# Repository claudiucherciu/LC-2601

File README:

# LibreCube LC-2601 GPS Module

## Overview
The LC-2601 GPS Module is a standalone board that integrates an
GPS receiver and makes its output in terms of position, altitude,
and time available via the CAN bus interface.

## Authors
* Claudiu Cherciu <claudiucherciu@gmail.com>
* Dominik Marszk <dmarszk@gmail.com>
* Artur Scholz <artur.scholz@cubesat.de>

## Acknowledgements
Supported by the ESOC Cybernetic Club.

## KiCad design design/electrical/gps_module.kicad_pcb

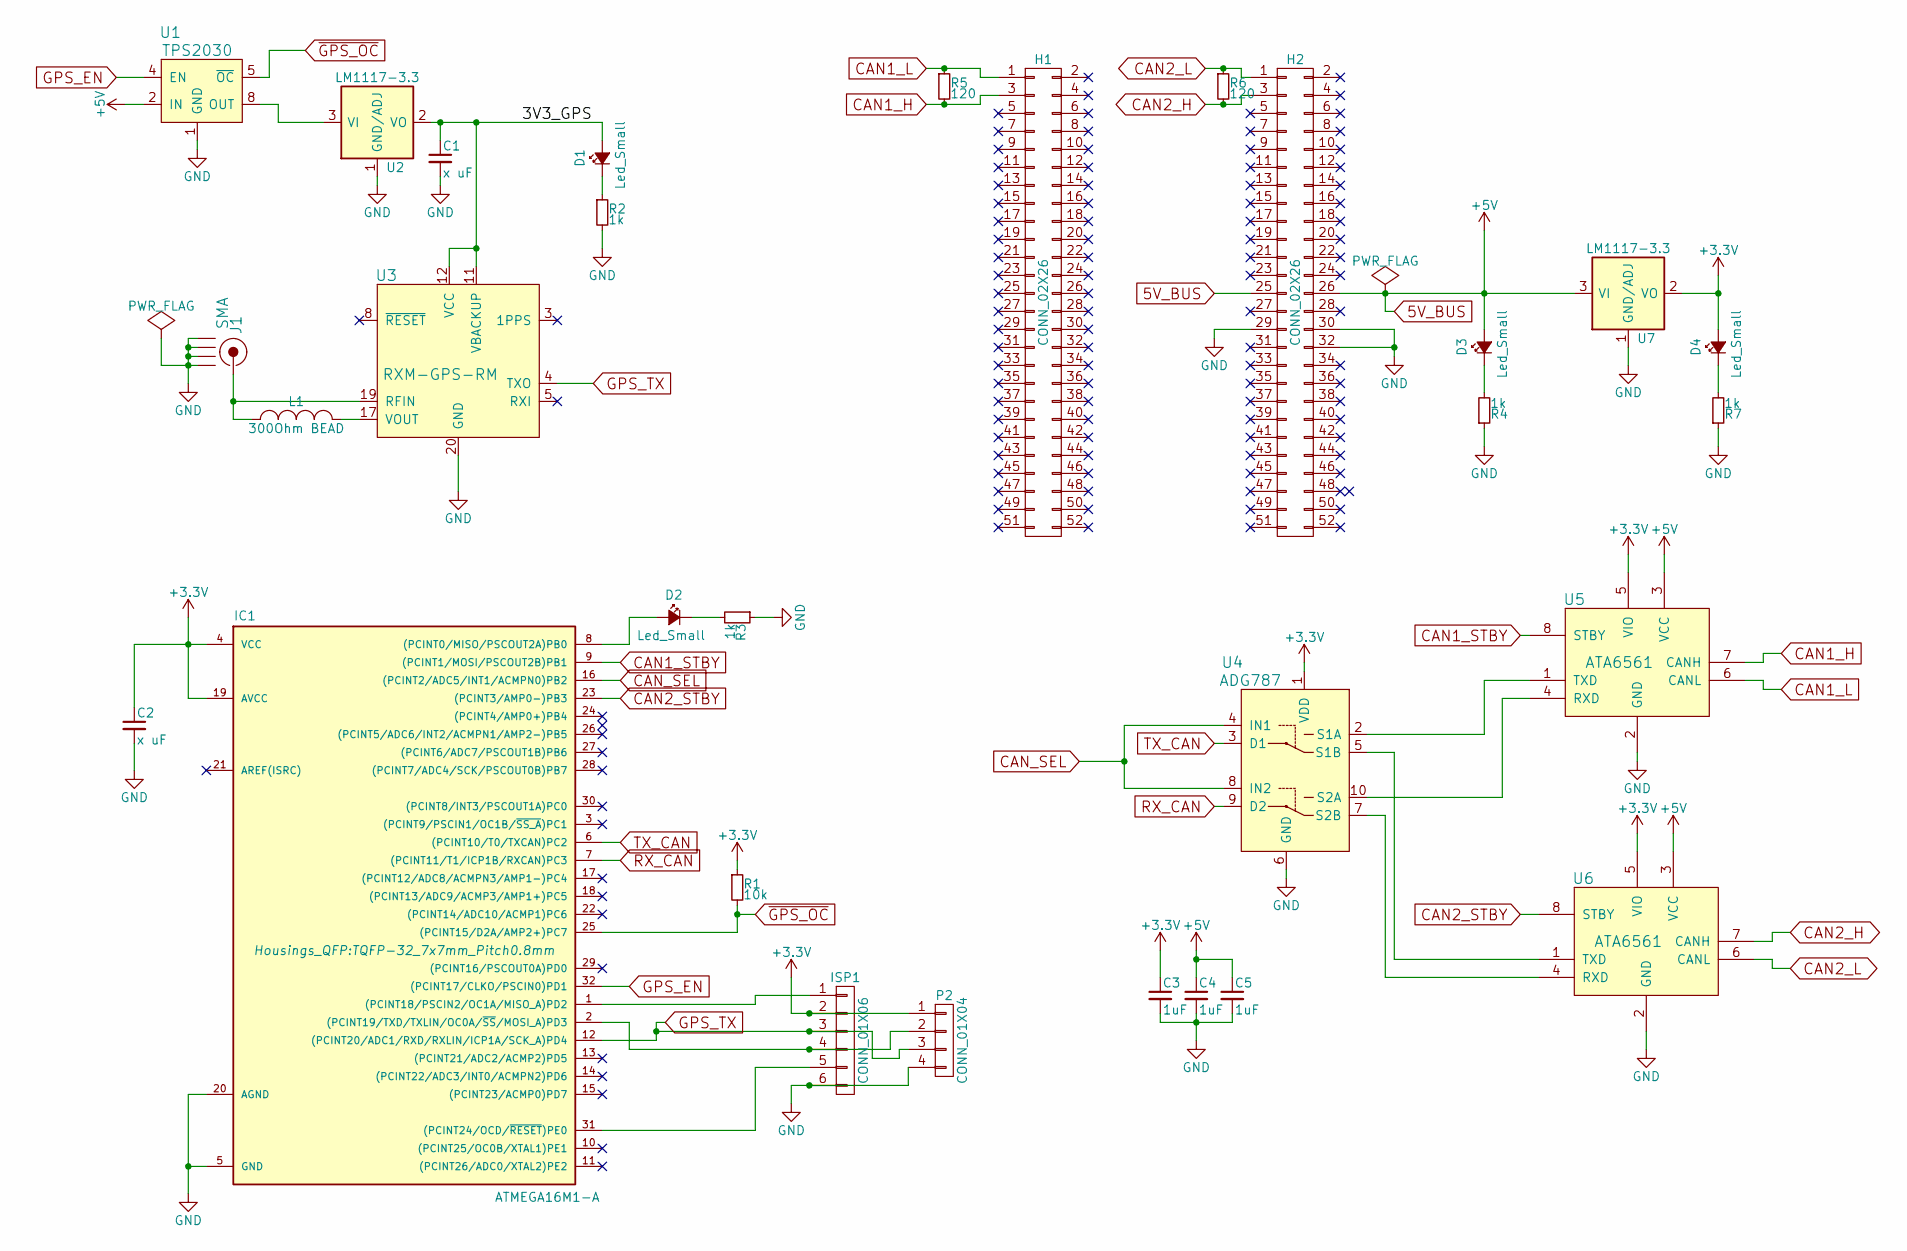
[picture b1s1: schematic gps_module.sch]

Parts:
C1, C2: x uF; C_0603
C3, C4, C5: 1uF; C_0603
D1, D2, D3, D4: Led_Small; LED_0805
H1, H2: CONN_02X26; Pin_Header_Straight_2x26
IC1: ATMEGA16M1-A; TQFP-32_7x7mm_Pitch0.8mm
ISP1: CONN_01X06; JST_GH_BM06B-GHS-TBT_06x1.25mm_Straight
J1: SMA
L1: 300Ohm BEAD; C_0603
P2: CONN_01X04; JST_GH_BM04B-GHS-TBT_04x1.25mm_Straight
R1: 10k; R_0603_HandSoldering
R2, R3, R4, R7: 1k; R_0603_HandSoldering
R5, R6: 120; R_0603_HandSoldering
U1: TPS2030; SO-8
U2, U7: LM1117-3.3; SOT-223
U3: RXM-GPS-RM
U4: ADG787; MSOP-10_3x3mm_Pitch0.5mm
U5, U6: ATA6561; SO-8

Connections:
5V_BUS: C4.1, C5.1, D3.2 (A), H2.25, H2.26, U1.2 (IN), U1.3 (IN), U5.3 (VCC), U6.3 (VCC), U7.3 (VI)
+3V3: C2.1, C3.1, D4.2 (A), IC1.4 (VCC), IC1.19 (AVCC), ISP1.2, P2.1, R1.1, U4.1 (VDD), U5.5 (VIO), U6.5 (VIO), U7.2 (VO), U7.4 (VO)
/3V3_GPS: C1.1, D1.2 (A), U2.2 (VO), U2.4 (VO), U3.11 (VBACKUP), U3.12 (VCC)
CAN1_H: H1.3, R5.2, U5.7 (CANH)
CAN1_L: H1.1, R5.1, U5.6 (CANL)
CAN1_STBY: IC1.9 ((PCINT1/MOSI/PSCOUT2B)PB1), U5.8 (STBY)
CAN2_H: H2.3, R6.2, U6.7 (CANH)
CAN2_L: H2.1, R6.1, U6.6 (CANL)
CAN2_STBY: IC1.23 ((PCINT3/AMP0-)PB3), U6.8 (STBY)
CAN_SEL: IC1.16 ((PCINT2/ADC5/INT1/ACMPN0)PB2), U4.4 (IN1), U4.8 (IN2)
GND: C1.2, C2.2, C3.2, C4.2, C5.2, H2.29, H2.30, H2.32, IC1.5 (GND), IC1.20 (AGND), ISP1.6, J1.2 (GND1), J1.3 (GND2), J1.4 (GND3), J1.5 (GND4), P2.4, R2.2, R3.1, R4.1, R7.1, U1.1 (GND), U2.1 (GND/ADJ), U3.18 (GND), U3.20 (GND), U3.21 (GND), U3.22 (GND), U4.6 (GND), U5.2 (GND), U6.2 (GND), U7.1 (GND/ADJ)
GPS_EN: IC1.32 ((PCINT17/CLKO/PSCIN0)PD1), U1.4 (EN)
GPS_TX: IC1.12 ((PCINT20/ADC1/RXD/RXLIN/ICP1A/SCK_A)PD4), ISP1.3, P2.3, U3.4 (TXO)
unnamed: D1.1 (K), R2.1
unnamed: D2.1 (K), R3.2
unnamed: D2.2 (A), IC1.8 ((PCINT0/MISO/PSCOUT2A)PB0)
unnamed: D3.1 (K), R4.2
unnamed: D4.1 (K), R7.2
unnamed: IC1.1 ((PCINT18/PSCIN2/OC1A/MISO_A)PD2), ISP1.1
unnamed: IC1.2 ((PCINT19/TXD/TXLIN/OC0A/~SS~/MOSI_A)PD3), ISP1.4, P2.2
unnamed: IC1.31 ((PCINT24/OCD/~RESET~)PE0), ISP1.5
unnamed: J1.1 (RF), L1.1, U3.19 (RFIN)
unnamed: L1.2, U3.17 (VOUT)
unnamed: U1.6 (OUT), U1.7 (OUT), U1.8 (OUT), U2.3 (VI)
unnamed: U4.2 (S1A), U5.1 (TXD)
unnamed: U4.5 (S1B), U6.1 (TXD)
unnamed: U4.7 (S2B), U6.4 (RXD)
unnamed: U4.10 (S2A), U5.4 (RXD)
RX_CAN: IC1.7 ((PCINT11/T1/ICP1B/RXCAN)PC3), U4.9 (D2)
TX_CAN: IC1.6 ((PCINT10/T0/TXCAN)PC2), U4.3 (D1)
~GPS_OC: IC1.25 ((PCINT15/D2A/AMP2+)PC7), R1.2, U1.5 (~OC)

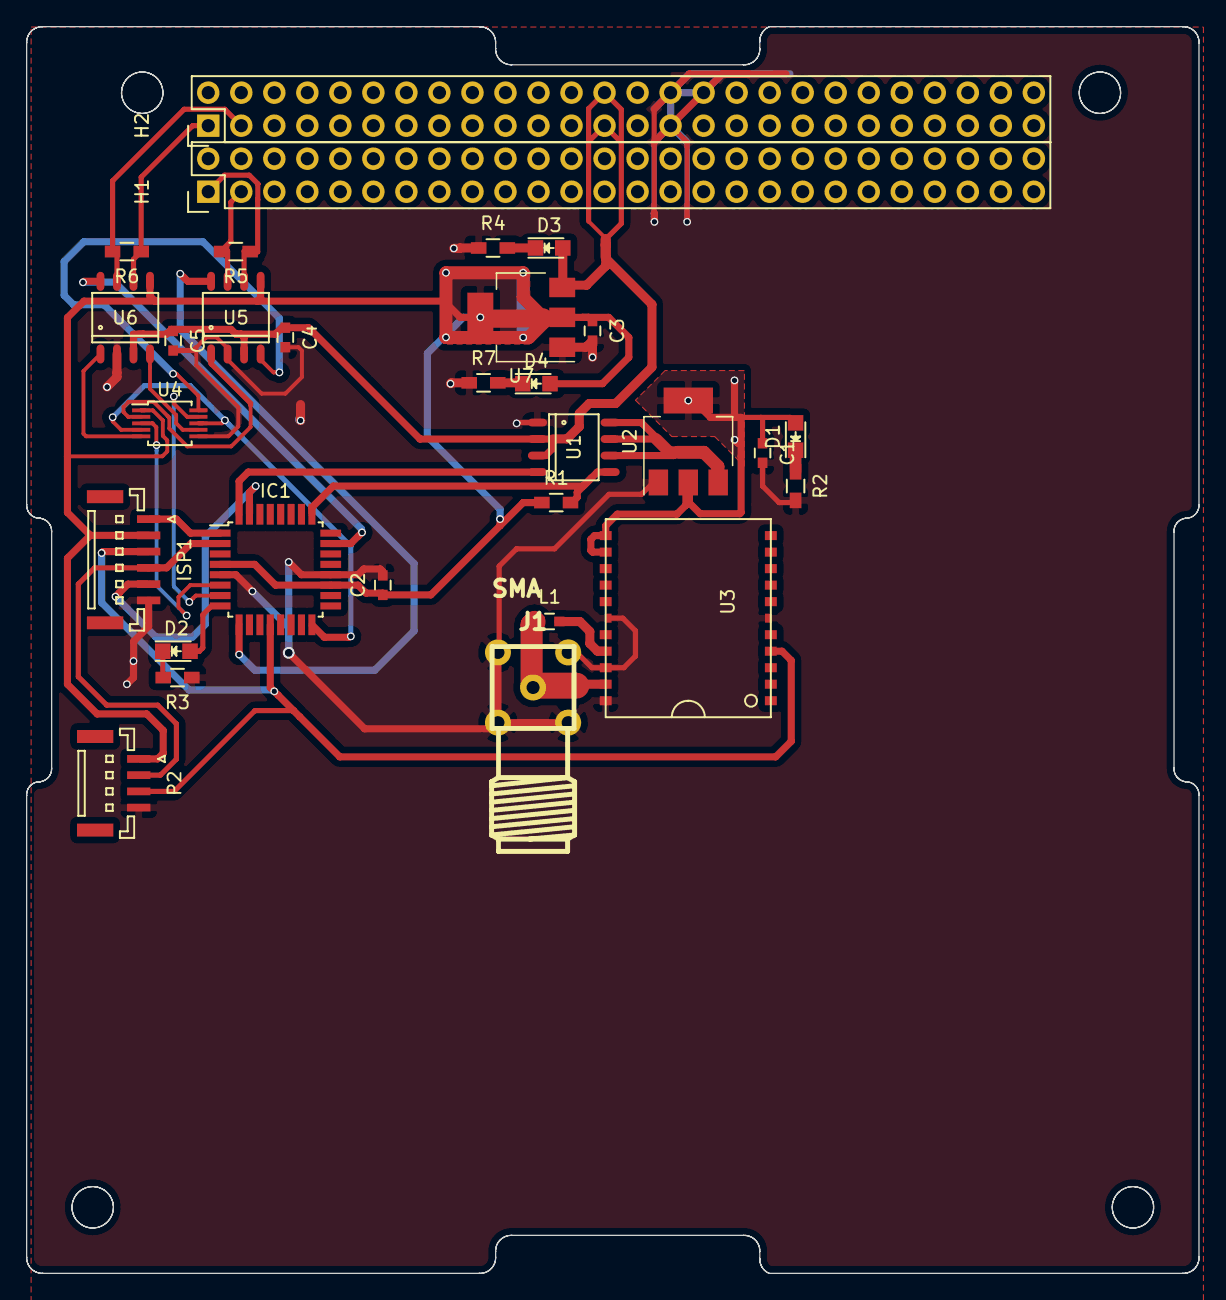
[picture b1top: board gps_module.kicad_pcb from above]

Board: 2 copper layers, 90.2 x 95.9 mm, 30 parts (0 on the bottom side), 31 nets.

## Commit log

2016-10-10 add .md file extension
2016-10-10 Initial add of kicad design files: sch, lib, some layout
2016-10-11 Renamed sch folder to /design/electrical
2016-10-11 Added ~GPS_OC as input signal to uC
2016-10-11 First layout attempt. Gerber files included.
2016-10-11 add firmware
2016-10-11 Removed voltage divider on GPS_RX, pullup resistor ~RESET for GPS and S3 & S4 as +5V supply. Added pullup resistor for ~GPS_OC. Solved most ERC errors.
2016-10-11 Changed pins function (direction) to solve ERC errors in schematics
2016-10-11 Updated PCB layout and Gerbers
2016-10-11 Removed temporary files from repository
2016-10-11 Added pad for alternative +5V supply.
2016-10-12 some folder rearrangement
2016-10-12 merge
2016-10-12 rename file
2016-10-14 Added decupling capacitors for CAN and MUX
2016-10-15 create new gerber files
2016-10-19 Rotated GPS module, increased GPS antenna track width
2016-12-09 Added Release notes/Changes tracking.
2016-12-09 Changed IC to 3.3V, added 1 LDO, 2 Leds, 1uart port, changed footprints to 0603, updated layout.
    Still 2 unconnected traces reported by Kicad.
2016-12-09 add 3v3 converter and LEDs
2016-12-09 fix unconnected track
